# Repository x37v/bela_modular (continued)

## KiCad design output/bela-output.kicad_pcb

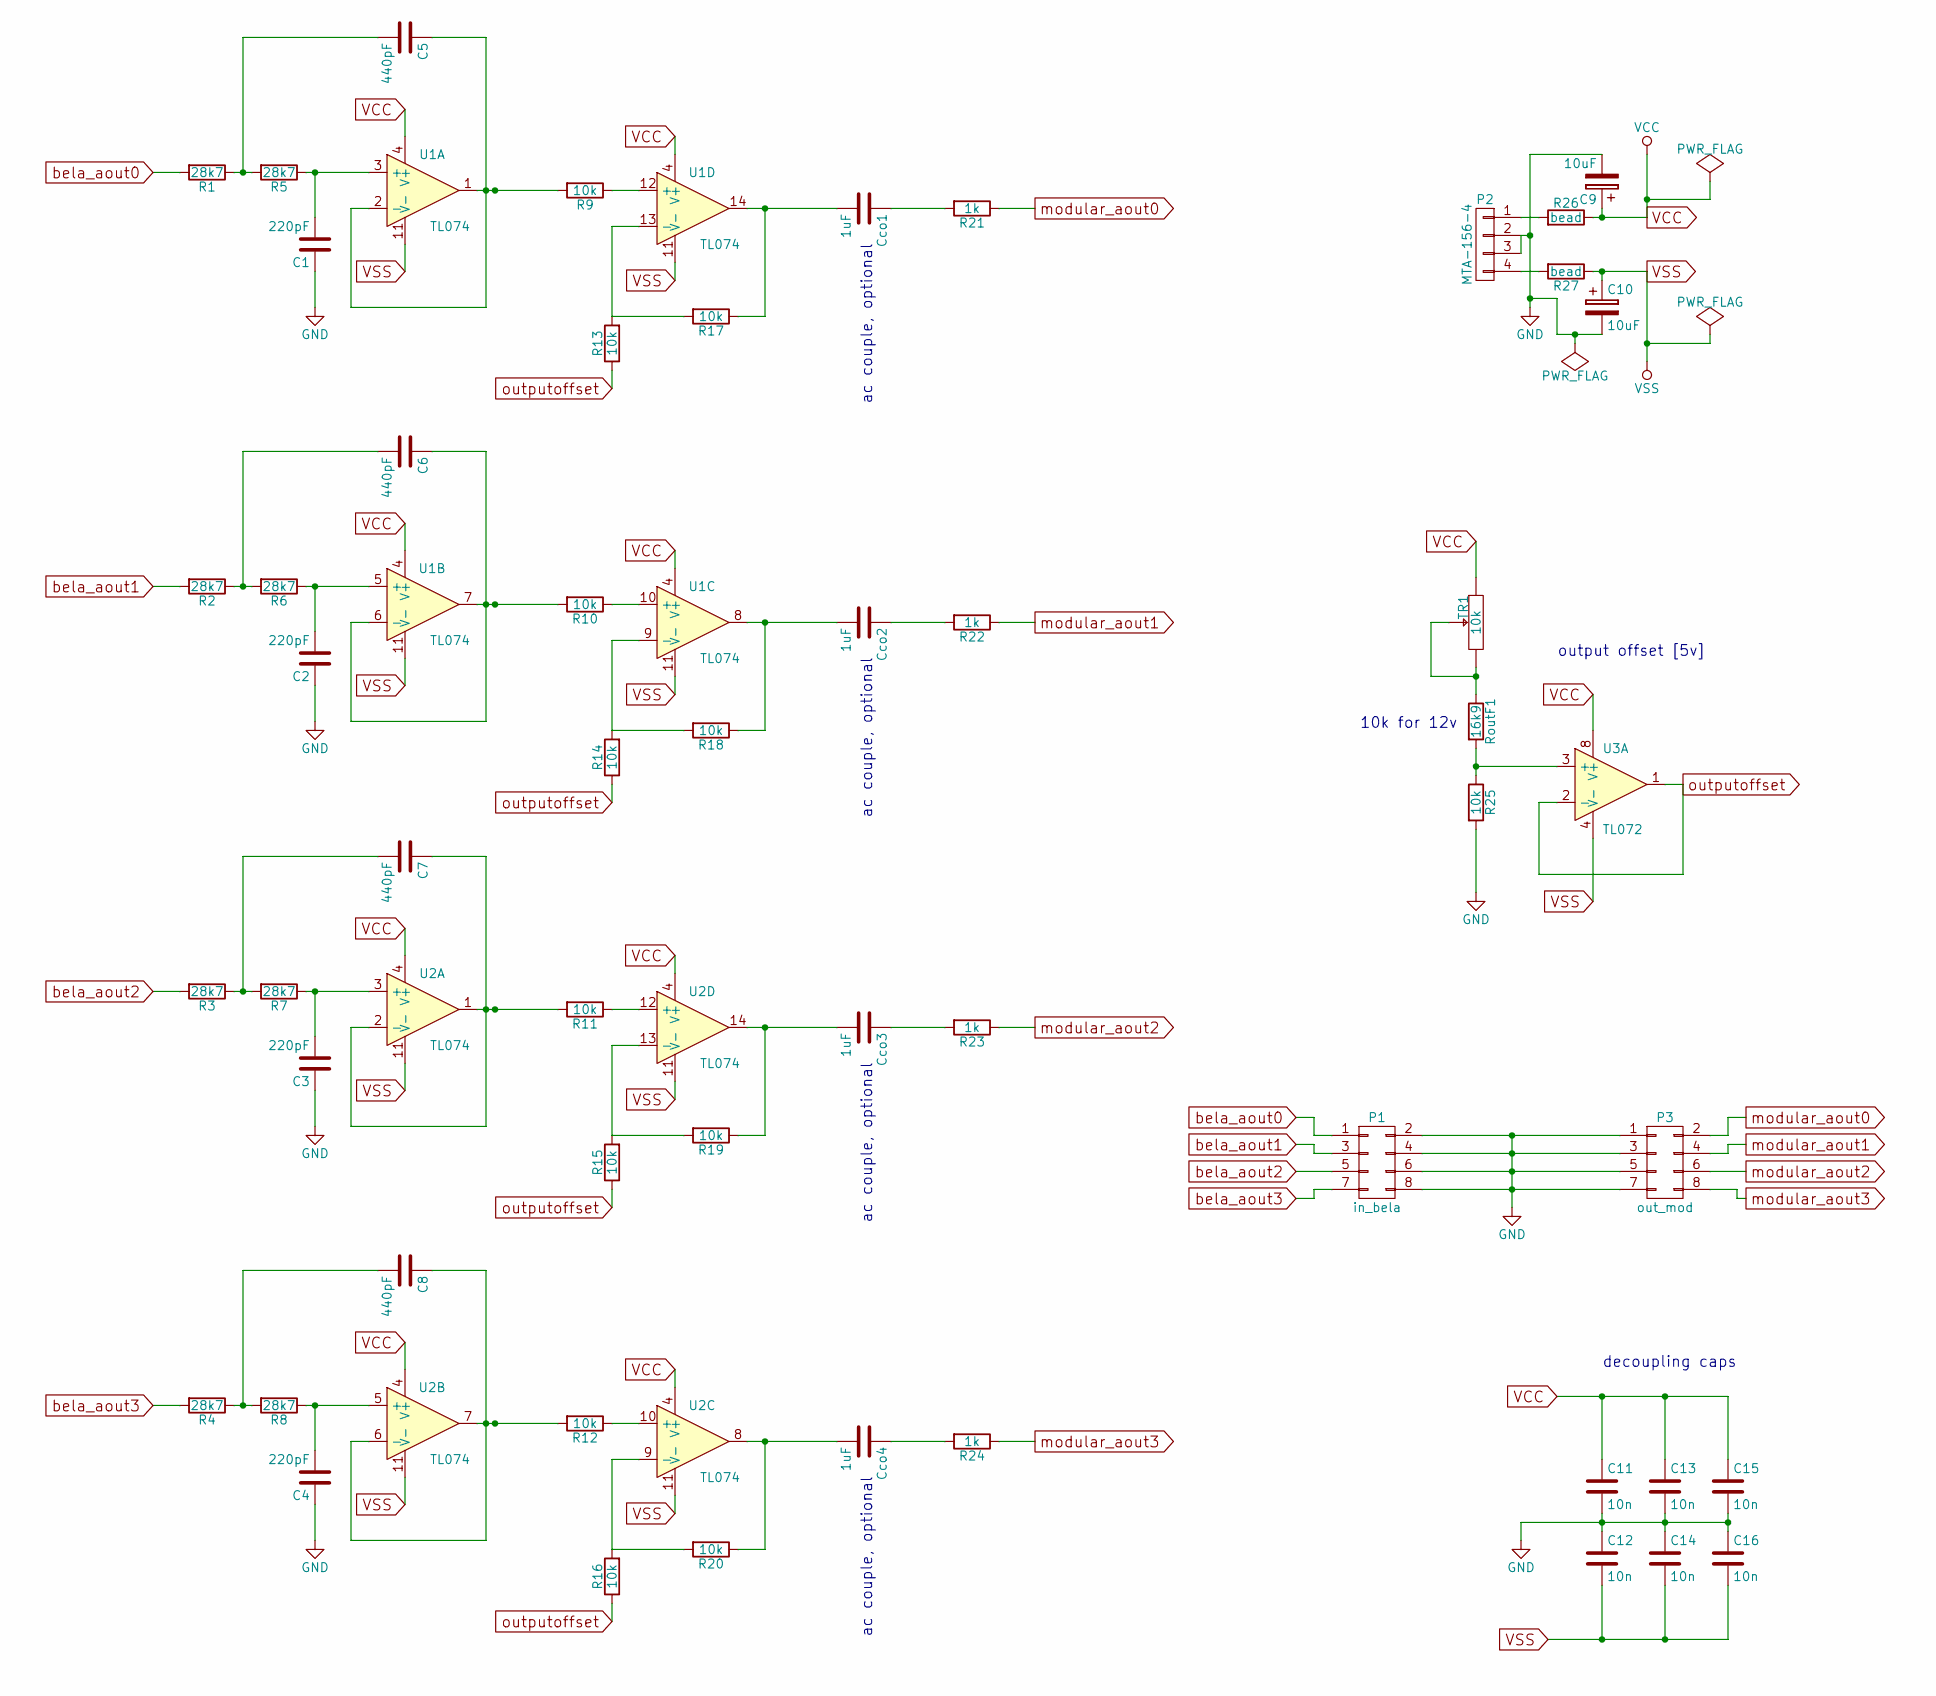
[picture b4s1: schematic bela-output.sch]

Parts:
C1, C2, C3, C4: 220pF; C_Rect_L4_W2.5_P2.5
C5, C6, C7, C8: 440pF; C_Rect_L4_W2.5_P2.5
C9, C10: 10uF; C_Radial_D5_L11_P2
C11, C12, C13, C14, C15, C16: 10n; C_Rect_L4_W2.5_P2.5
Cco1, Cco2, Cco3, Cco4: 1uF; C_Rect_L4_W2.5_P2.5
P1: in_bela; Pin_Header_Straight_2x04
P2: MTA-156-4
P3: out_mod; Pin_Header_Straight_2x04
R1, R2, R3, R4, R5, R6, R7, R8: 28k7; Resistor_Horizontal_RM10mm
R9, R10, R11, R12, R13, R14, R15, R16, R17, R18, R19, R20, R25: 10k; Resistor_Horizontal_RM10mm
R21, R22, R23, R24: 1k; Resistor_Horizontal_RM10mm
R26, R27: bead; Resistor_Vertical_RM5mm
RoutF1: 16k9; Resistor_Horizontal_RM10mm
TR1: 10k; trimmer
U1, U2: TL074; DIP-14_W7.62mm_LongPads
U3: TL072; DIP-8_W7.62mm_LongPads

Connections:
GND: C1.1, C2.1, C3.1, C4.1, C9.2, C10.2, C11.2, C12.1, C13.2, C14.1, C15.2, C16.1, P1.2, P1.4, P1.6, P1.8, P2.2, P2.3, P3.1, P3.3, P3.5, P3.7, R25.2
unnamed: C1.2, R5.1, U1.3 (+)
unnamed: C2.2, R6.1, U1.5 (+)
unnamed: C3.2, R7.1, U2.3 (+)
unnamed: C4.2, R8.1, U2.5 (+)
unnamed: C5.1, R9.2, U1.1, U1.2 (-)
unnamed: C5.2, R1.1, R5.2
unnamed: C6.1, R10.2, U1.6 (-), U1.7
unnamed: C6.2, R2.1, R6.2
unnamed: C7.1, R11.2, U2.1, U2.2 (-)
unnamed: C7.2, R3.1, R7.2
unnamed: C8.1, R12.2, U2.6 (-), U2.7
unnamed: C8.2, R4.1, R8.2
unnamed: Cco1.1, R21.2
unnamed: Cco1.2, R17.1, U1.14
unnamed: Cco2.1, R22.2
unnamed: Cco2.2, R18.1, U1.8
unnamed: Cco3.1, R23.2
unnamed: Cco3.2, R19.1, U2.14
unnamed: Cco4.1, R24.2
unnamed: Cco4.2, R20.1, U2.8
unnamed: P2.1, R26.2
unnamed: P2.4, R27.2
unnamed: R9.1, U1.12 (+)
unnamed: R10.1, U1.10 (+)
unnamed: R11.1, U2.12 (+)
unnamed: R12.1, U2.10 (+)
unnamed: R13.2, R17.2, U1.13 (-)
unnamed: R14.2, R18.2, U1.9 (-)
unnamed: R15.2, R19.2, U2.13 (-)
unnamed: R16.2, R20.2, U2.9 (-)
unnamed: R25.1, RoutF1.2, U3.3 (+)
unnamed: RoutF1.1, TR1.2, TR1.3
VCC: C9.1, C11.1, C13.1, C15.1, R26.1, TR1.1, U1.4 (V+), U2.4 (V+), U3.8 (V+)
VSS: C10.1, C12.2, C14.2, C16.2, R27.1, U1.11 (V-), U2.11 (V-), U3.4 (V-)
bela_aout0: P1.1, R1.2
bela_aout1: P1.3, R2.2
bela_aout2: P1.5, R3.2
bela_aout3: P1.7, R4.2
modular_aout0: P3.2, R21.1
modular_aout1: P3.4, R22.1
modular_aout2: P3.6, R23.1
modular_aout3: P3.8, R24.1
outputoffset: R13.1, R14.1, R15.1, R16.1, U3.1, U3.2 (-)

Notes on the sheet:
ac couple, optional
10k for 12v
output offset [5v]
decoupling caps

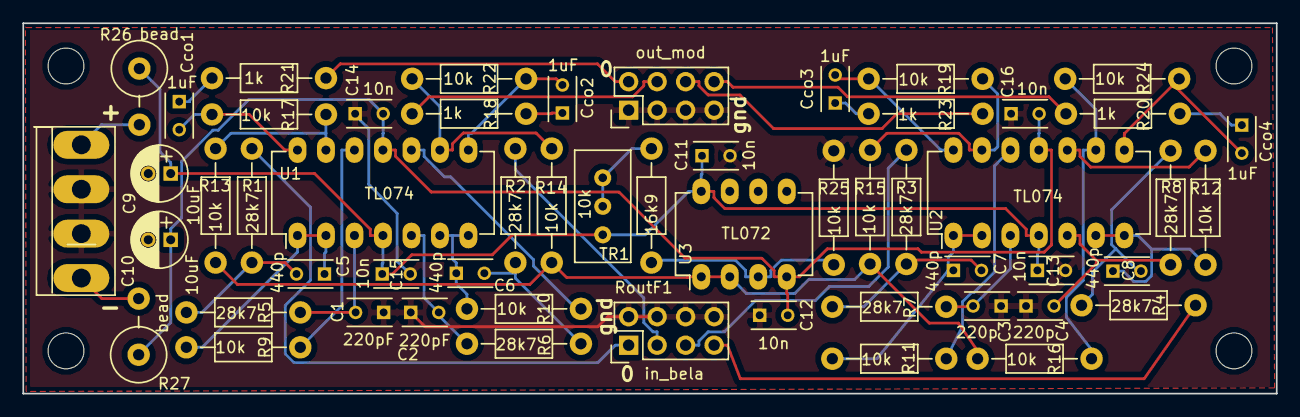
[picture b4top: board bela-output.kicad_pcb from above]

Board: 2 copper layers, 111.8 x 33.0 mm, 59 parts (0 on the bottom side), 44 nets.

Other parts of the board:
REF1, REF2, REF3, REF4: MountingHole_3.2mm_M3

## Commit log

2016-12-03 initial schematic
2016-12-04 created an input only project, moved other to all
2016-12-05 major updates! nearly done with input
2016-12-05 created readme.. nothing really going on yet
2016-12-06 moved things around, moved more to F.SilkS
2016-12-06 added more PCB documentation and moved some stuff
2016-12-06 working on analog output pcb
2016-12-11 mostly layed out, veridical resistors
2016-12-11 flush resistor layout
2016-12-11 added top filled gnd zone
2016-12-11 moved text for output
2016-12-11 relayout of input
2016-12-11 added gnd and 0 and 10k on trim
2016-12-13 more useful readme stuff
2016-12-13 more readme
2016-12-19 last part for the digital + ac coupled
2016-12-19 more updates, mostly notes and input/output direction changes
2016-12-24 added + for polar caps
2016-12-30 oops, forgot to connect the grounds
2016-12-30 connected up grounds on input board
2017-01-03 much more work on vfd [2 parallel interfaces]
2017-01-03 a bunch more hooking up
2017-01-03 added pulldowns for digital inputs
2017-01-04 a lot more layout work
2017-01-04 starting pcb layout a little
2017-01-05 moving along, still no idea why 5v is hooked to 3.3v
2017-01-06 fixed up some footprint issues
2017-01-06 3.3v is no longer connected to 5v!
2017-01-08 added decoupling caps, power expand, more layout
2017-01-08 more layout, gonna split into 2 boards
2017-01-08 moved ac over to its own board
2017-01-08 consolidated schematics etc
2017-01-08 removed ac from extra, added power connection for 15
2017-01-08 added trimmer, removed b.s., almost ready to route
2017-01-08 totally routed, added labels
2017-01-08 moved some labels to make things more clear
2017-01-08 changed visibility
2017-01-08 fixed up labeling
2017-01-08 all layed out
2017-01-30 exchanged bad parts on ac board, though haven't placed yet
2017-01-31 Revert "exchanged bad parts on ac board, though haven't placed yet"
    This reverts commit 3185bdf4a96cd7a989377c24179a0fe5be16ab20.
2017-01-31 got the correct part in, AND the mounting holes
2017-02-08 working with enables on extra board
2017-02-10 ditched power, remapped a bunch of io
    should have all the emmc and lcd lines disabled at boot
2017-03-03 connected up the rest of the extra board
2017-03-03 fixed up some labels
2017-04-23 updated pin mapping
2017-04-23 table formatting?
2017-04-23 headed
2017-04-23 fixed numbering
2017-04-24 vfd io docs
2017-04-24 finished table
2017-04-24 center??
2017-04-24 added gpio specs
2017-04-24 added note
2017-04-24 updated readme and added code dep
2017-04-26 updated readme with rework
